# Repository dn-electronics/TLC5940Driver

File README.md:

TLC5940Driver
=============
Introduction
============
The TLC5940Driver is a development board can be used to investigate the capabilities of upto 3 TLC5940 LED driver chips using an Atmel ATMEGA88

Features
========
1. Reprogrammable ATMEGA88 microcontroller
2. Upto 3 TLC5940 LED drivers
3. Dimming control switch inputs
4. Soft latching power ON/OFF
5. Demo HEX file to fade 16 LEDs (TLC5940Driver-1xTLC5940.hex)
6. Demo HEX file to fade 48 LEDs (TLC5940Driver-3xTLC5940.hex)

Licence
=======
<p>This work is licensed under a <a href="http://www.creativecommons.org/licenses/by-sa/3.0" target="_blank">Creative Commons Attribution-ShareAlike 3.0 Unported License</a> 

Schematic
=========

LEDPlate
========

Programming File Fuse Settings - ATMEGA88 
=========================================

1. BOOTSZ: 1024W_0C00
2. SPIEN: tick
3. EESAVE: tick
4. BODLEVEL: DISABLED
5. CKOUT: tick
6. SUT_CKSEL: INTROSC_8MHZ_6CK_14CK_65MS
7. EXT:  F9
8. HIGH: D7
9. LOW:  A2

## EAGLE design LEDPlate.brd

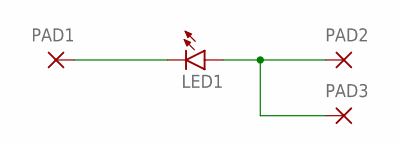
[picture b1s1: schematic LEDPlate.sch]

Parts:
LED1: LED2; P-C8WT803
PAD1, PAD2, PAD3: PAD; P-SMD1.27X2.54

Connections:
unnamed: LED1.C, PAD1.1
unnamed: LED1.A, PAD2.1, PAD3.1

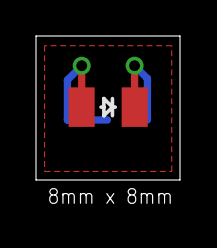
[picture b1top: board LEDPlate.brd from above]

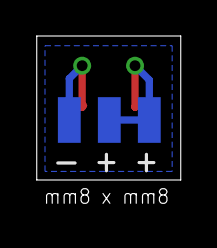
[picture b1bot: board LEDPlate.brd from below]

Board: 2 copper layers, 8.0 x 8.0 mm, 4 parts (3 on the bottom side), 2 nets.

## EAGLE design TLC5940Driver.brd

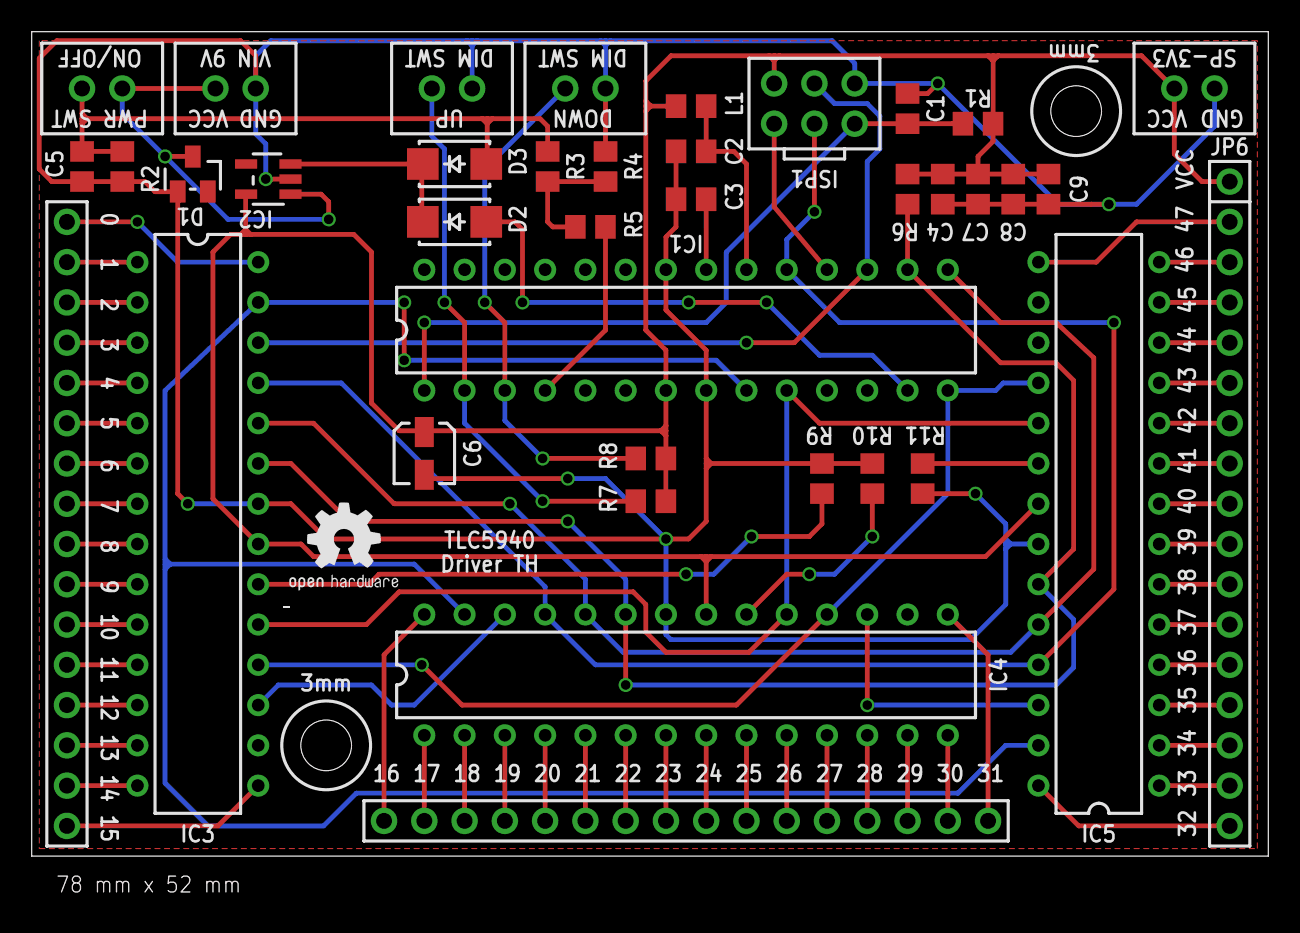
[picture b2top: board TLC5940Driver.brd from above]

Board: 2 copper layers, 78.0 x 52.0 mm, 40 parts (0 on the bottom side), 74 nets.

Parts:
C1, C2, C3, C4, C5, C7, C8, C9: 100nF; P-0805
C6: 2.2uF; P-CAPNICHICON-3MM
D1: P-SOT23-3
D2, D3: MBRA140; P-SMA
GOLD_ORB_SM1: OSHWLOGO_GOLD_ORB_SM; OSHW2
IC1: ATMEGA88PA; P-DIL28
IC2: SPX3819; P-SOT23-5E
IC3, IC4, IC5: TLC5940; P-DIL28
ISP1: P-AVRISPSHROUDED
JP1, JP2: P-JST-XH-1X02
JP3, JP4, JP5: P-1X16
JP6: P-1X01
L1: P-0805
R1: 4K7; P-0805
R2: 100K; P-0805
R3: 27K; P-0805
R4: 15K; P-0805
R5: 150R; P-0805
R6, R7, R8: 10K; P-0805
R9, R10, R11: 7K8; P-0805
SW1, SW2, SW3: P-JST-XH-1X02-VERT

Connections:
GND: C1.2, C2.2, C3.2, C4.2, C5.2, C6.2, C7.2, C8.2, C9.2, D1.1, IC1.8, IC1.22, IC2.2, IC3.22, IC4.22, IC5.22, ISP1.GND, JP1.1, JP2.2, R2.1, R4.1, R9.1, R10.1, R11.1, SW2.2, SW3.2
unnamed: D1.3, IC2.1, JP1.2, SW1.1
unnamed: C5.1, D3.A, R2.2, R3.2, SW1.2
unnamed: IC3.28, JP3.1
unnamed: D2.K, D3.K, IC2.3
unnamed: IC3.1, JP3.2
unnamed: IC3.2, JP3.3
unnamed: IC3.3, JP3.4
unnamed: IC3.4, JP3.5
unnamed: IC3.5, JP3.6
unnamed: IC3.6, JP3.7
unnamed: IC3.7, JP3.8
unnamed: IC3.8, JP3.9
unnamed: IC3.9, JP3.10
unnamed: IC3.10, JP3.11
unnamed: IC3.11, JP3.12
unnamed: IC3.12, JP3.13
unnamed: IC3.13, JP3.14
unnamed: IC3.14, JP3.15
unnamed: IC3.15, JP3.16
unnamed: IC4.28, JP4.1
unnamed: IC4.1, JP4.2
unnamed: IC4.2, JP4.3
unnamed: IC4.3, JP4.4
unnamed: IC4.4, JP4.5
unnamed: IC4.5, JP4.6
unnamed: IC4.6, JP4.7
unnamed: IC4.7, JP4.8
unnamed: IC4.8, JP4.9
unnamed: IC4.9, JP4.10
unnamed: IC4.10, JP4.11
unnamed: IC4.11, JP4.12
unnamed: IC4.12, JP4.13
unnamed: IC4.13, JP4.14
unnamed: IC4.14, JP4.15
unnamed: IC4.15, JP4.16
unnamed: IC5.28, JP5.1
unnamed: IC5.1, JP5.2
unnamed: IC5.2, JP5.3
unnamed: IC5.3, JP5.4
unnamed: IC5.4, JP5.5
unnamed: IC5.5, JP5.6
unnamed: IC5.6, JP5.7
unnamed: IC5.7, JP5.8
unnamed: IC5.8, JP5.9
unnamed: IC5.9, JP5.10
unnamed: IC5.10, JP5.11
unnamed: IC5.11, JP5.12
unnamed: IC5.12, JP5.13
unnamed: IC5.13, JP5.14
unnamed: IC5.14, JP5.15
unnamed: IC5.15, JP5.16
unnamed: IC1.16, IC3.23, IC4.23, IC5.23, R6.1
unnamed: D2.A, IC1.13
unnamed: IC1.2, R7.1, SW3.1
unnamed: C1.1, IC1.1, ISP1.RST, R1.1
unnamed: C2.1, IC1.20, L1.1
unnamed: C3.1, IC1.21
unnamed: IC1.19, IC3.25, IC4.25, IC5.25, ISP1.SCK
unnamed: IC1.18, ISP1.MISO
unnamed: IC1.17, IC3.26, ISP1.MOSI
unnamed: IC1.4, R5.2
unnamed: IC1.3, R8.1, SW2.1
unnamed: IC5.20, R11.2
unnamed: IC3.17, IC4.26
unnamed: IC4.17, IC5.26
unnamed: IC1.15, IC3.24, IC4.24, IC5.24
unnamed: IC1.14, IC3.18, IC4.18, IC5.18
unnamed: IC1.10, IC3.19, IC4.19, IC5.19
unnamed: IC1.9, IC3.27, IC4.27, IC5.27
unnamed: IC4.20, R10.2
unnamed: R3.1, R4.2, R5.1
unnamed: IC3.20, R9.2
VCC: C4.1, C6.1, C7.1, C8.1, C9.1, IC1.7, IC2.5, IC3.21, IC4.21, IC5.21, ISP1.VCC, JP2.1, JP6.1, L1.2, R1.2, R6.2, R7.2, R8.2

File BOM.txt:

Partlist

Assembly variant: 

Part     Value          Package            

C1       100nF          P-0805             
C2       100nF          P-0805             
C3       100nF          P-0805             
C4       100nF          P-0805             
C5       100nF          P-0805             
C6       2.2uF          P-CAPNICHICON-3MM  
C7       100nF          P-0805             
C8       100nF          P-0805             
C9       100nF          P-0805             
D1       MMBZ5245BLT1G  P-SOT23-3          
D2       MBRA140        P-SMA              
D3       MBRA140        P-SMA              
IC1      ATMEGA88PA     P-DIL28            
IC2      SPX3819        P-SOT23-5E         
IC3      TLC5940        P-DIL28            
IC4      TLC5940        P-DIL28            
IC5      TLC5940        P-DIL28            
ISP1     6pin Header    P-AVRISPSHROUDED   
JP1                     P-JST-XH-1X02      
JP2                     P-JST-XH-1X02      
L1       BLM21AG102SN1D P-0805             
R1       4K7            P-0805             
R2       100K           P-0805             
R3       27K            P-0805             
R4       15K            P-0805             
R5       150R           P-0805             
R6       10K            P-0805             
R7       10K            P-0805             
R8       10K            P-0805             
R9       7K8            P-0805             
R10      7K8            P-0805             
R11      7K8            P-0805             
SW1                     P-JST-XH-1X02-VERT 
SW2                     P-JST-XH-1X02-VERT 
SW3                     P-JST-XH-1X02-VERT
